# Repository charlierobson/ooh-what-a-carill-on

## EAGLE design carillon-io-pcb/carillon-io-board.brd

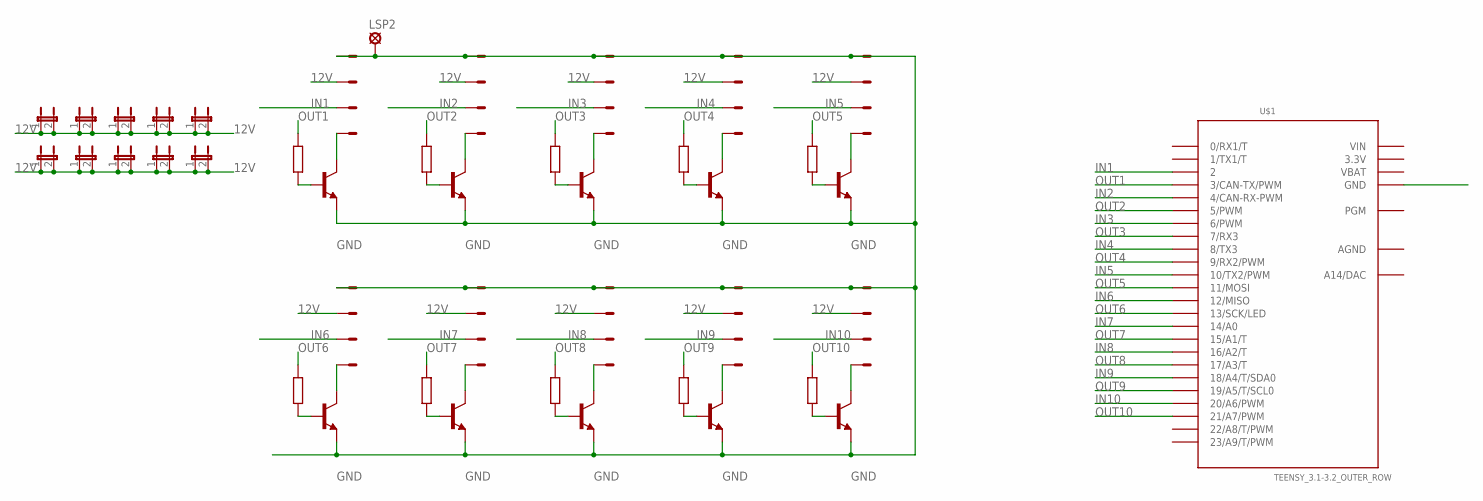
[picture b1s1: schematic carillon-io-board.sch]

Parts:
J1, J2, J3, J4, J5, J6, J7, J8, J9, J10: 22-05-7048-04; 7395-04
JP1, JP2, JP3, JP4, JP5, JP6, JP7, JP8, JP9, JP10: JP1E; JP1
LSP2: LSP10
R1, R3, R5, R7, R9, R11, R13, R15, R17, R19: R-EU_0207/10; 0207/10
T1, T2, T3, T4, T5, T6, T7, T8, T9, T10: 2N3904; TO92
U$1: TEENSY_3.1-3.2_OUTER_ROW; TEENSY_3.0-3.2&LC_OUTER_ROW

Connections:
3.3V: U$1.3.3V, U$1.3.3V1 (3.3V)
12V: J1.2, J2.2, J3.2, J4.2, J5.2, J6.2, J7.2, J8.2, J9.2, J10.2, JP1.1, JP1.2, JP2.1, JP2.2, JP3.1, JP3.2, JP4.1, JP4.2, JP5.1, JP5.2, JP6.1, JP6.2, JP7.1, JP7.2, JP8.1, JP8.2, JP9.1, JP9.2, JP10.1, JP10.2
AGND: U$1.AGND
GND: J1.1, J2.1, J3.1, J4.1, J5.1, J6.1, J7.1, J8.1, J9.1, J10.1, LSP2.MP, T1.3 (E), T2.3 (E), T3.3 (E), T4.3 (E), T5.3 (E), T6.3 (E), T7.3 (E), T8.3 (E), T9.3 (E), T10.3 (E)
IN1: J1.3, U$1.2
IN2: J2.3, U$1.4 (4/CAN-RX-PWM)
IN3: J3.3, U$1.6 (6/PWM)
IN4: J4.3, U$1.8 (8/TX3)
IN5: J5.3, U$1.10 (10/TX2/PWM)
IN6: J6.3, U$1.12 (12/MISO)
IN7: J7.3, U$1.14/A0
IN8: J8.3, U$1.16/A2 (16/A2/T)
IN9: J9.3, U$1.18/A4 (18/A4/T/SDA0)
IN10: J10.3, U$1.20/A6 (20/A6/PWM)
unnamed: J1.4, T1.1 (C)
unnamed: J6.4, T6.1 (C)
unnamed: J2.4, T2.1 (C)
unnamed: J3.4, T3.1 (C)
unnamed: J4.4, T4.1 (C)
unnamed: J5.4, T5.1 (C)
unnamed: J7.4, T7.1 (C)
unnamed: J8.4, T8.1 (C)
unnamed: J9.4, T9.1 (C)
unnamed: J10.4, T10.1 (C)
unnamed: U$1.GND, U$1.GND1 (GND)
OUT1: R1.1, U$1.3 (3/CAN-TX/PWM)
OUT2: R3.1, U$1.5 (5/PWM)
OUT3: R5.1, U$1.7 (7/RX3)
OUT4: R7.1, U$1.9 (9/RX2/PWM)
OUT5: R9.1, U$1.11 (11/MOSI)
OUT6: R11.1, U$1.13 (13/SCK/LED)
OUT7: R13.1, U$1.15/A1 (15/A1/T)
OUT8: R15.1, U$1.17/A3 (17/A3/T)
OUT9: R17.1, U$1.19/A5 (19/A5/T/SCL0)
OUT10: R19.1, U$1.21/A7 (21/A7/PWM)
T1: R1.2, T1.2 (B)
T2: R3.2, T2.2 (B)
T3: R5.2, T3.2 (B)
T4: R7.2, T4.2 (B)
T5: R9.2, T5.2 (B)
T6: R11.2, T6.2 (B)
T7: R13.2, T7.2 (B)
T8: R15.2, T8.2 (B)
T9: R17.2, T9.2 (B)
T10: R19.2, T10.2 (B)
VBAT: U$1.VBAT
VIN: U$1.VIN

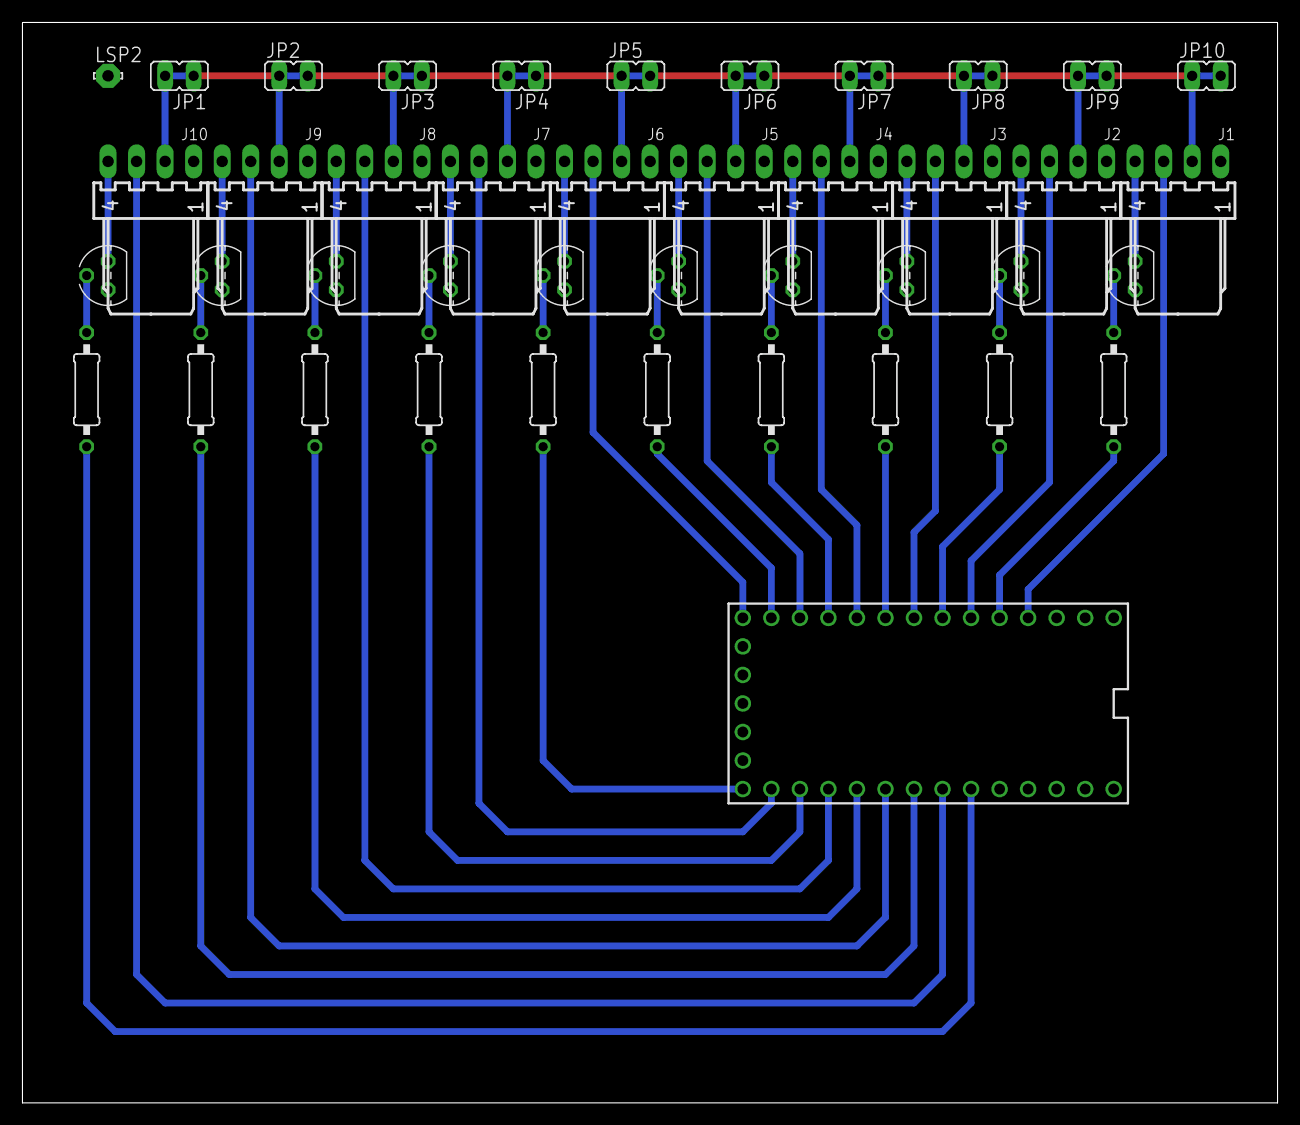
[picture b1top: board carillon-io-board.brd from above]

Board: 2 copper layers, 111.7 x 96.2 mm, 42 parts (0 on the bottom side), 44 nets.

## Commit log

2019-11-25 working v1
2019-11-26 rename files, add primitive browser
2019-11-26 add chooser
2019-11-27 all bells
2019-11-27 use sample clips, grinds to halt
2019-11-27 midi
2019-11-27 first edit
2019-11-27 note distribution
2019-11-28 first look at mapping
2019-11-28 more maps
2019-11-29 adding all maps.txts
2019-11-29 add names to maptxtxs
2019-12-03 adding io board (wrong currently)
2019-12-03 fix board
2019-12-04 io board proved, firmware file added
2019-12-04 move pcb
2019-12-06 rename host folder
2019-12-06 move to states as objects
2019-12-09 arduino command parser
2019-12-09 move processing out to separate classes
2019-12-09 renaming data
2019-12-10 move controllers into midiinfo
2019-12-10 rm ds_store
2019-12-10 serial test in place, working
2019-12-10 buttons collected every frome for arduino
2019-12-10 buttons ahoy!
2019-12-11 go full midi.
2019-12-11 handle end of tune properly
2019-12-13 Add player simulation
2019-12-13 add simulation mode
2019-12-13 tidy up, no crash on missing serial, adding map file parsing
2019-12-13 add some stats
2019-12-16 fix split
2019-12-17 fix noteshare
2019-12-17 some tune edits
2019-12-17 target tv resolution 1920x1080
2019-12-17 add bell anim, split out controller to own file
2019-12-17 rebuild after lost changes
2019-12-17 the bells!
2019-12-17 add lyrics
2019-12-17 mondo midi mapping
2019-12-17 LYRICS
2019-12-18 edits
2019-12-18 make tune names prettier
2019-12-18 moving to queue of notes in controller
2019-12-18 start queueing note off
2019-12-18 ready screen joke
2019-12-18 lyrics paging
2019-12-18 lyrics changes
2019-12-18 double page lyrics
2019-12-18 improve title screen
2019-12-19 move stats to controllers, json export
2019-12-19 puds!
2019-12-19 title light flash and score draw
2019-12-19 fix score reporting bug
2019-12-20 new balls please
